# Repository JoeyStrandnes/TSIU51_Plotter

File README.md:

# Skittle Sort

Skittle sort är en sorteringsmaskin för kursen "Mikrodatorprojektet".

- 2x Servomotorer
- 2x ATMega16A
- 3D printad trumma 
- jm162a 2x16 numerisk LCD
- TCS34725 (RGB sensor)

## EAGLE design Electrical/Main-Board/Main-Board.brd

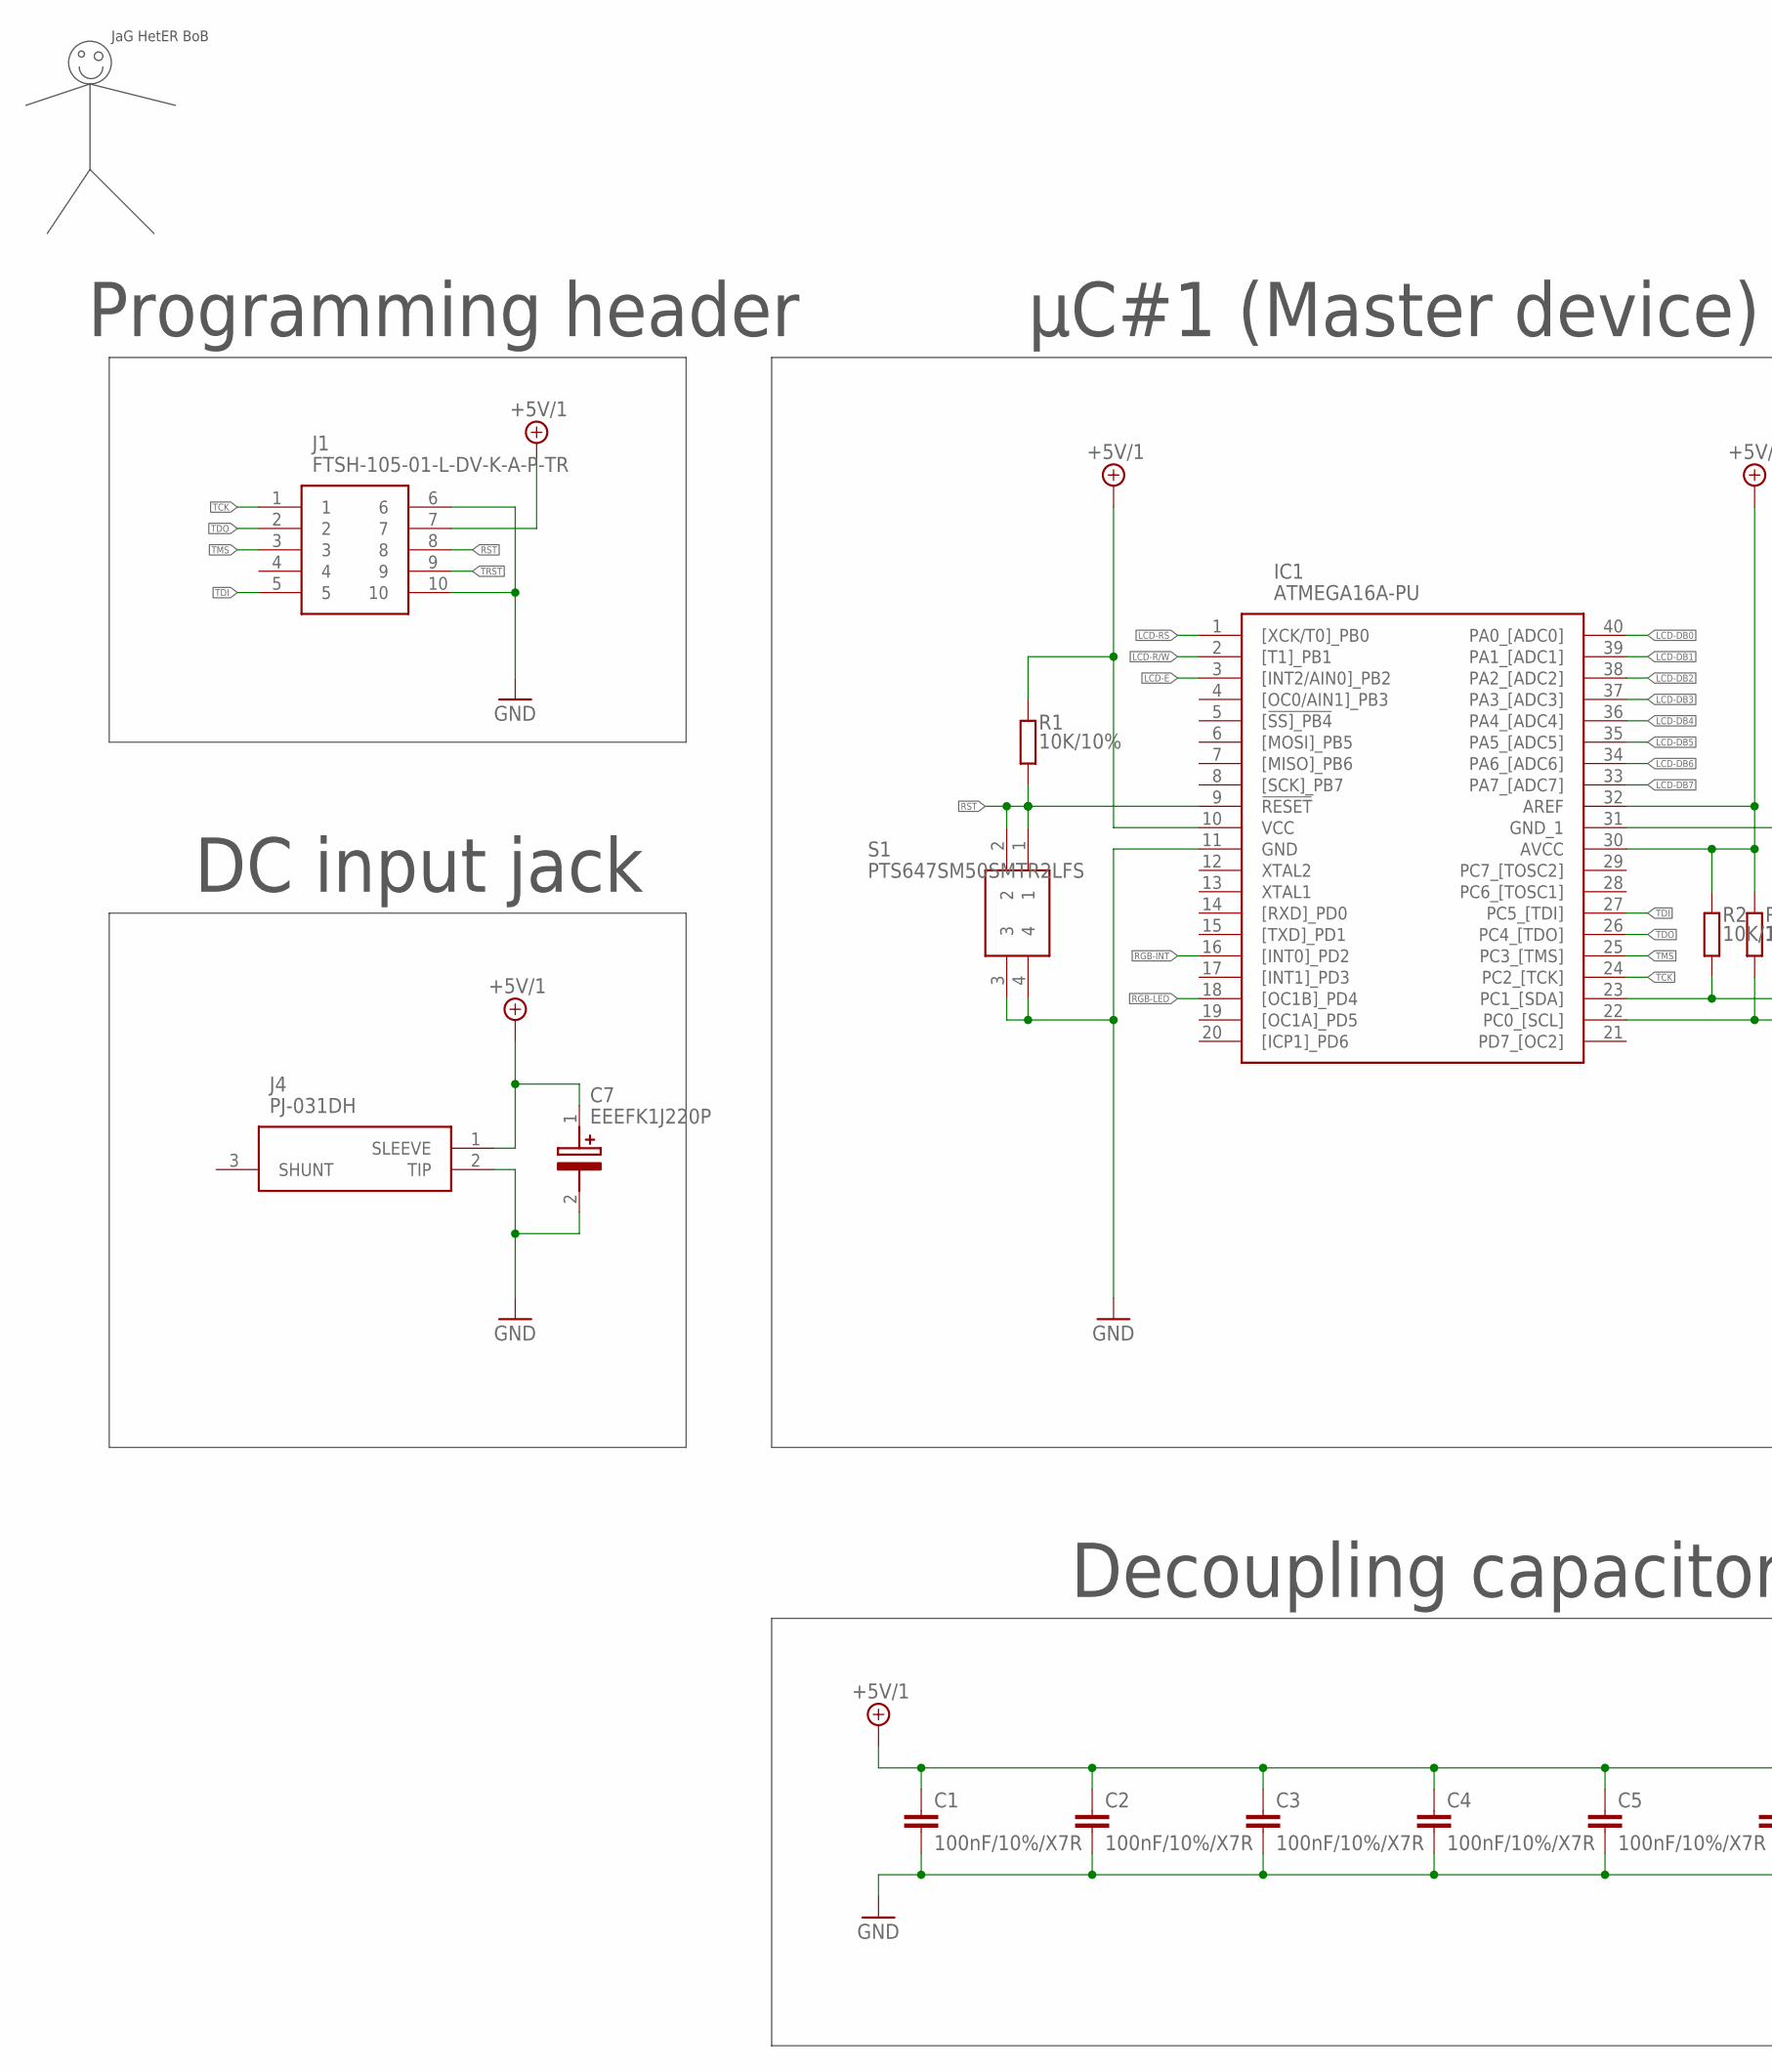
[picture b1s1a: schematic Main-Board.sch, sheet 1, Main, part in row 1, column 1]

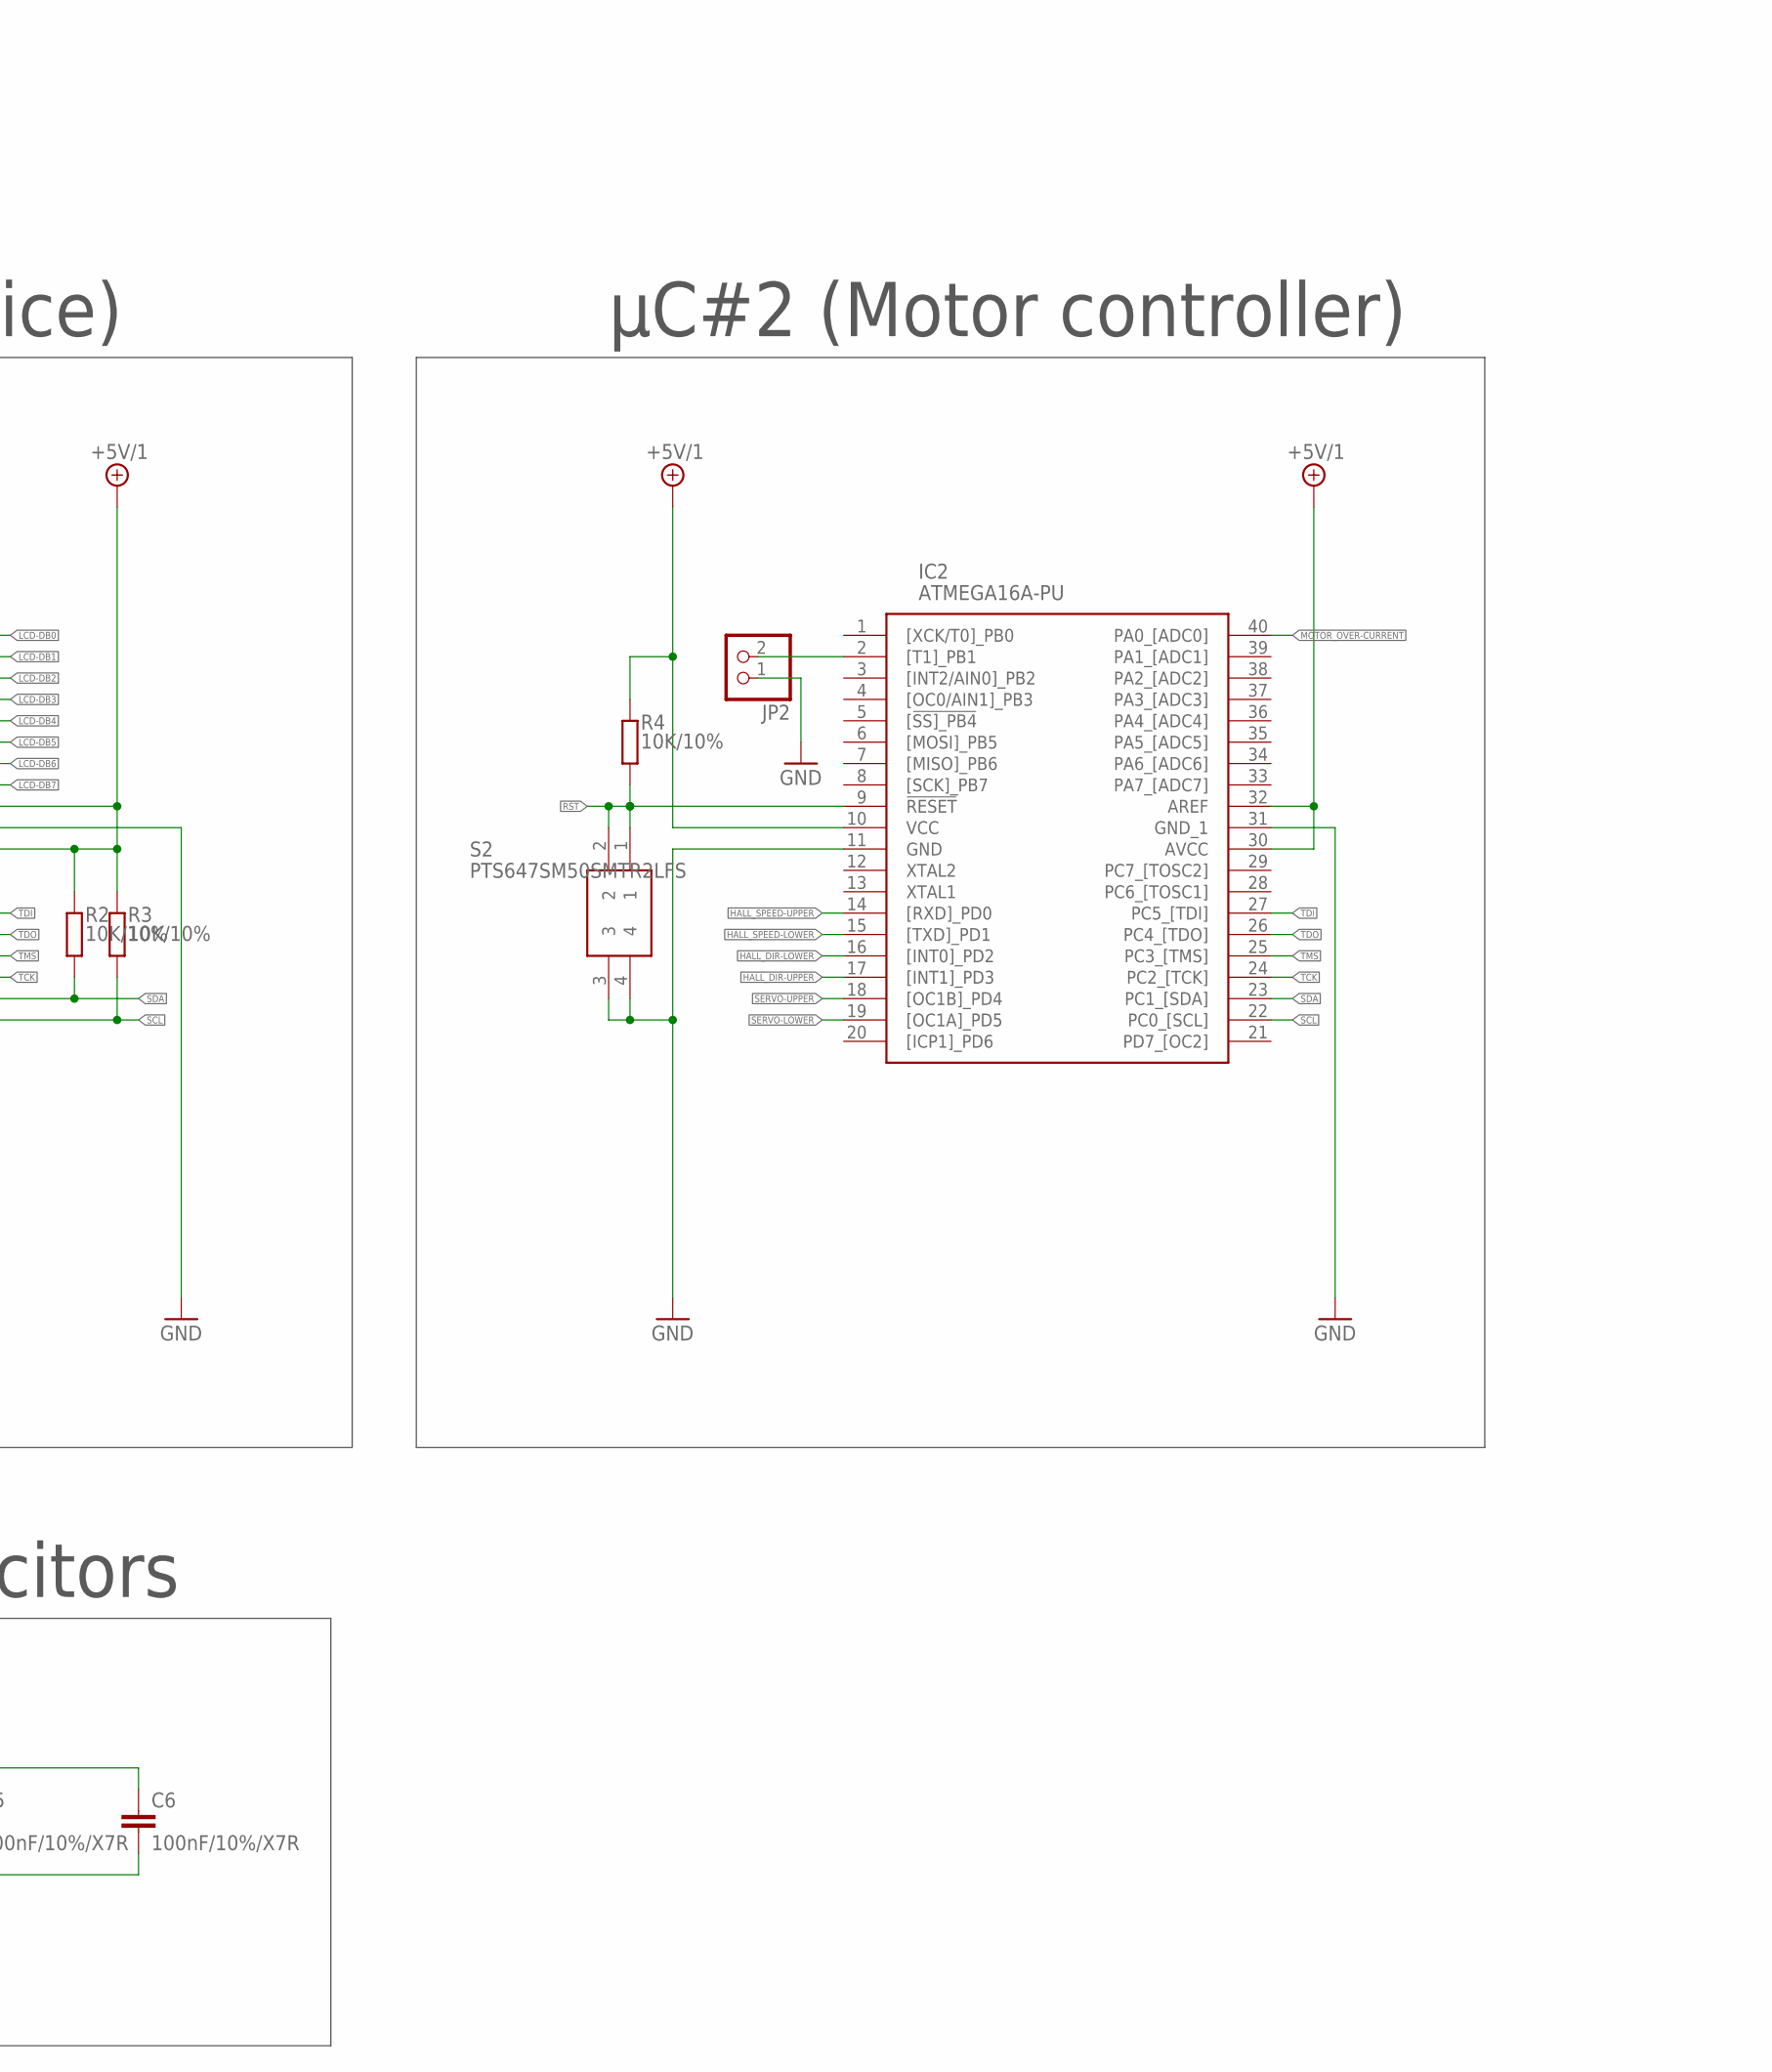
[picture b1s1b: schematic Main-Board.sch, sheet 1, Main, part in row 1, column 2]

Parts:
C1, C2, C3, C4, C5, C6: 100nF/10%/X7R; C0603
C7: EEEFK1J220P; CAPAE800X650N
IC1, IC2: ATMEGA16A-PU; DIP1556W56P254L5232H483Q40N
J1: FTSH-105-01-L-DV-K-A-P-TR; FTSH10501LDVKAPTR
J4: PJ-031DH; PJ031DH
JP2: PINHD-1X2; 1X02
R1, R2, R3, R4: 10K/10%; R0603
S1, S2: PTS647SM50SMTR2LFS

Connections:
+5V/1: C1.1, C2.1, C3.1, C4.1, C5.1, C6.1, C7.1 (+), IC1.10 (VCC), IC1.30 (AVCC), IC1.32 (AREF), IC2.10 (VCC), IC2.30 (AVCC), IC2.32 (AREF), J1.7, J4.1 (SLEEVE), R1.2, R2.2, R3.2, R4.2; also elsewhere on the board
GND: C1.2, C2.2, C3.2, C4.2, C5.2, C6.2, C7.2 (-), IC1.11 (GND), IC1.31 (GND_1), IC2.11 (GND), IC2.31 (GND_1), J1.6, J1.10, J4.2 (TIP), JP2.1, S1.3, S1.4, S2.3, S2.4; also elsewhere on the board
HALL_DIR-LOWER: IC2.16 ([INT0]_PD2); also elsewhere on the board
HALL_DIR-UPPER: IC2.17 ([INT1]_PD3); also elsewhere on the board
HALL_SPEED-LOWER: IC2.15 ([TXD]_PD1); also elsewhere on the board
HALL_SPEED-UPPER: IC2.14 ([RXD]_PD0); also elsewhere on the board
LCD-DB0: IC1.40 (PA0_[ADC0]); also elsewhere on the board
LCD-DB1: IC1.39 (PA1_[ADC1]); also elsewhere on the board
LCD-DB2: IC1.38 (PA2_[ADC2]); also elsewhere on the board
LCD-DB3: IC1.37 (PA3_[ADC3]); also elsewhere on the board
LCD-DB4: IC1.36 (PA4_[ADC4]); also elsewhere on the board
LCD-DB5: IC1.35 (PA5_[ADC5]); also elsewhere on the board
LCD-DB6: IC1.34 (PA6_[ADC6]); also elsewhere on the board
LCD-DB7: IC1.33 (PA7_[ADC7]); also elsewhere on the board
LCD-E: IC1.3 ([INT2/AIN0]_PB2); also elsewhere on the board
LCD-R/W: IC1.2 ([T1]_PB1); also elsewhere on the board
LCD-RS: IC1.1 ([XCK/T0]_PB0); also elsewhere on the board
MOTOR_OVER-CURRENT: IC2.40 (PA0_[ADC0]); also elsewhere on the board
unnamed: IC2.2 ([T1]_PB1), JP2.2
RGB-INT: IC1.16 ([INT0]_PD2); also elsewhere on the board
RGB-LED: IC1.18 ([OC1B]_PD4); also elsewhere on the board
RST: IC1.9 (!RESET), IC2.9 (!RESET), J1.8, R1.1, R4.1, S1.1, S1.2, S2.1, S2.2
SCL: IC1.22 (PC0_[SCL]), IC2.22 (PC0_[SCL]), R3.1; also elsewhere on the board
SDA: IC1.23 (PC1_[SDA]), IC2.23 (PC1_[SDA]), R2.1; also elsewhere on the board
SERVO-LOWER: IC2.19 ([OC1A]_PD5); also elsewhere on the board
SERVO-UPPER: IC2.18 ([OC1B]_PD4); also elsewhere on the board
TCK: IC1.24 (PC2_[TCK]), IC2.24 (PC2_[TCK]), J1.1
TDI: IC1.27 (PC5_[TDI]), IC2.27 (PC5_[TDI]), J1.5
TDO: IC1.26 (PC4_[TDO]), IC2.26 (PC4_[TDO]), J1.2
TMS: IC1.25 (PC3_[TMS]), IC2.25 (PC3_[TMS]), J1.3
TRST: J1.9

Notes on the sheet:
JaG HetER BoB
Programming header
µC#1 (Master device)
µC#2 (Motor controller)
DC input jack
Decoupling capacitors

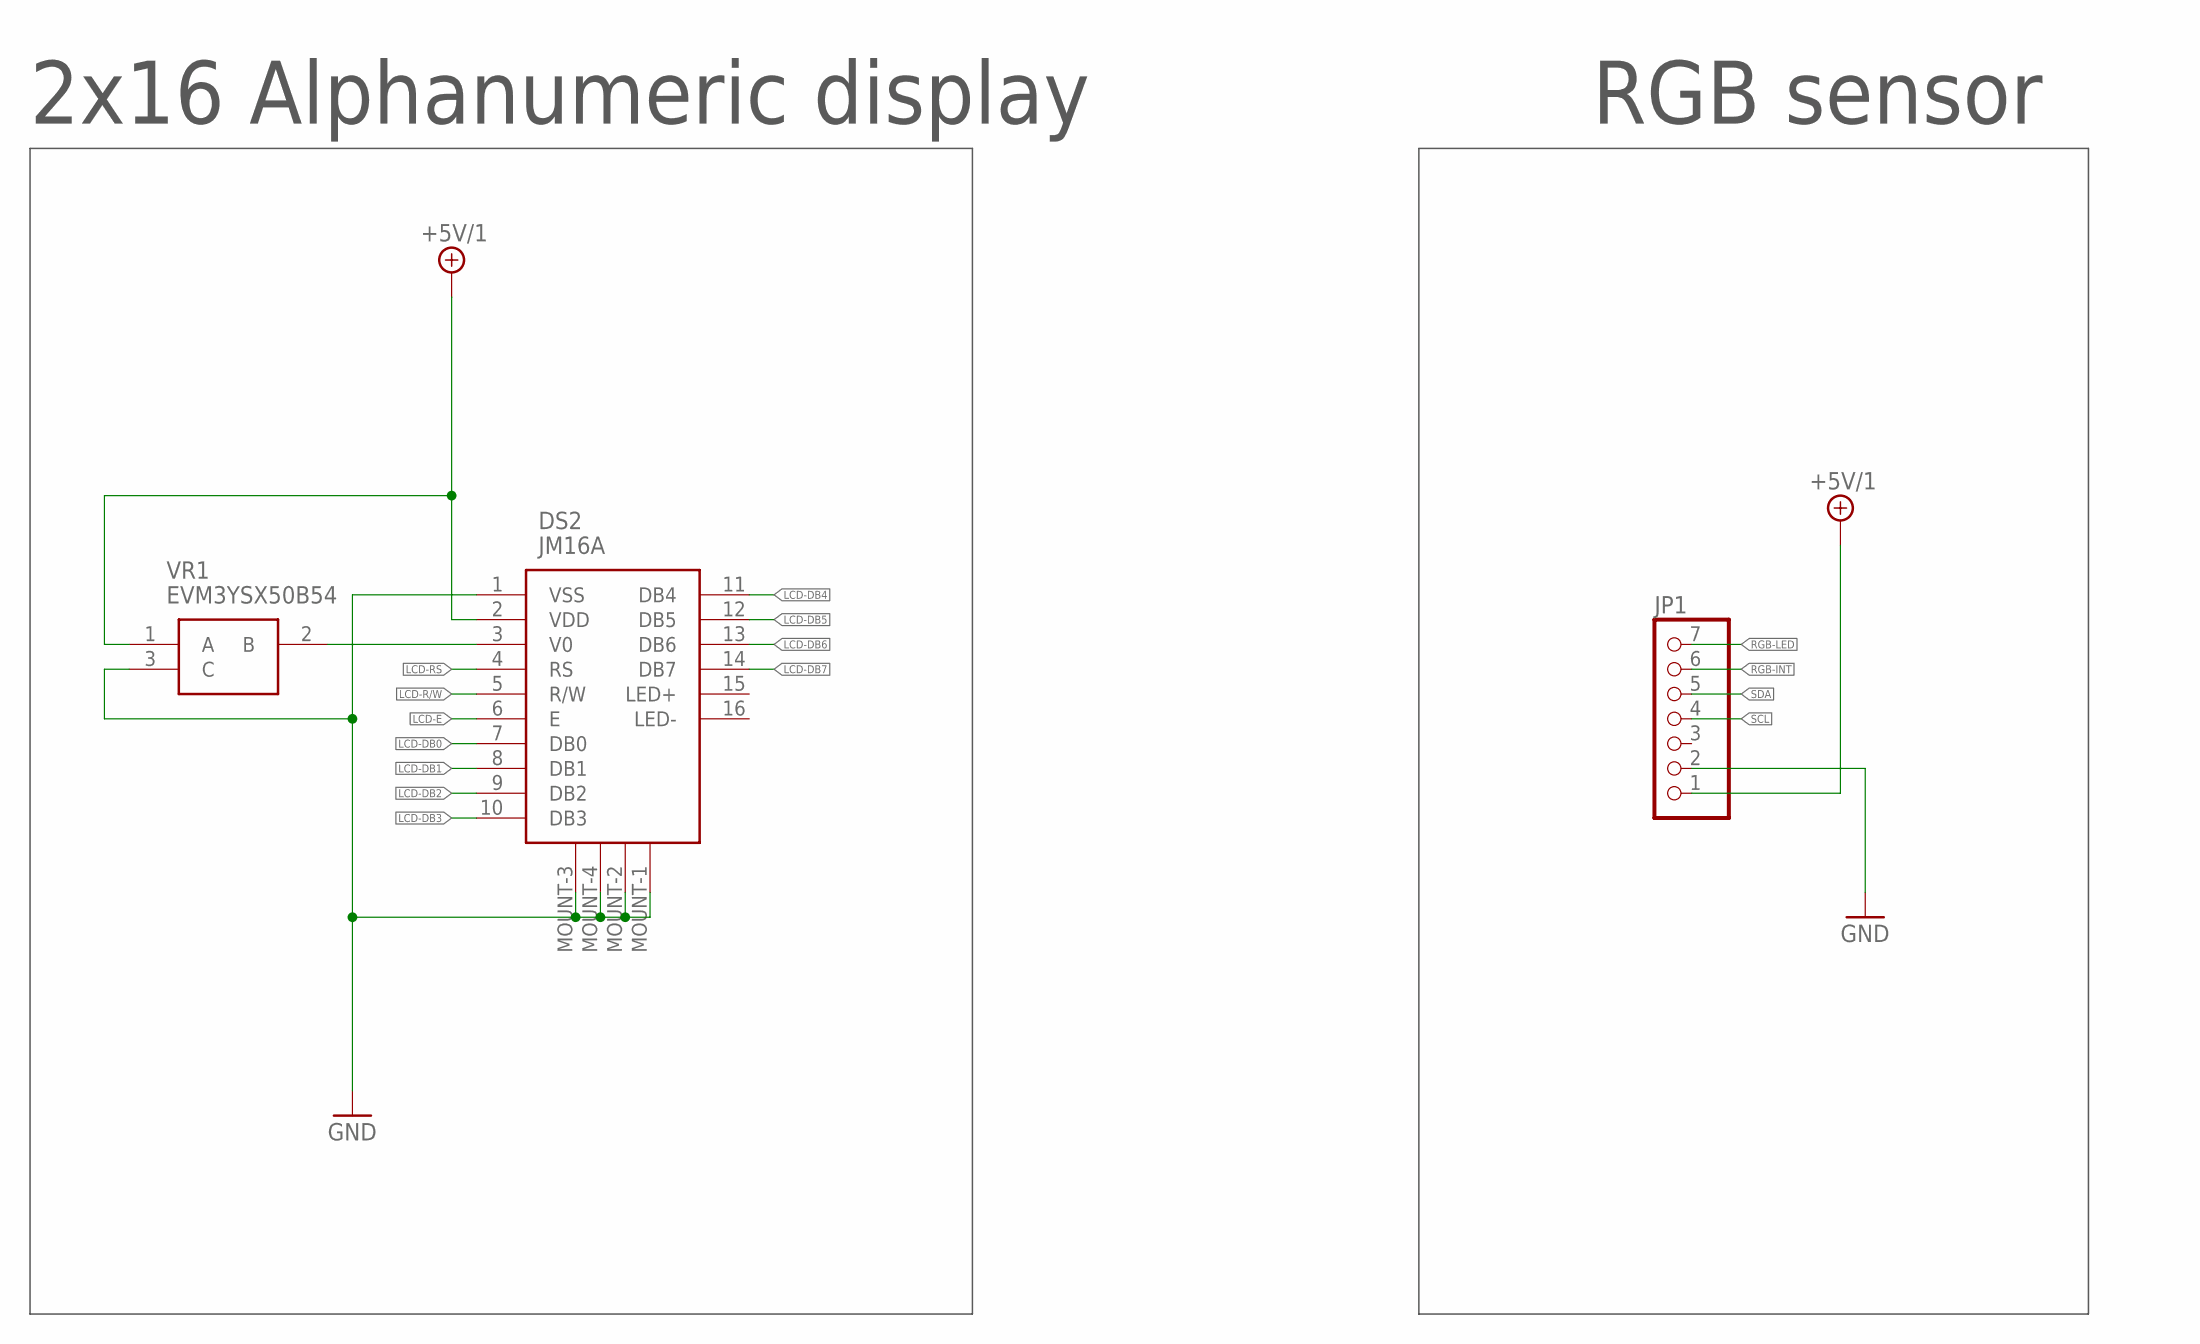
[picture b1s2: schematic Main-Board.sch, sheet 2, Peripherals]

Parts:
DS2: JM16A
JP1: PINHD-1X7; 1X07
VR1: EVM3YSX50B54

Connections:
+5V/1: DS2.2 (VDD), JP1.1, VR1.1 (A); also elsewhere on the board
GND: DS2.1 (VSS), DS2.MOUNT-1 (MOUNT-4), DS2.MOUNT-2 (MOUNT-3), DS2.MOUNT-3 (MOUNT-1), DS2.MOUNT-4 (MOUNT-2), JP1.2, VR1.3 (C); also elsewhere on the board
LCD-DB0: DS2.7 (DB0); also elsewhere on the board
LCD-DB1: DS2.8 (DB1); also elsewhere on the board
LCD-DB2: DS2.9 (DB2); also elsewhere on the board
LCD-DB3: DS2.10 (DB3); also elsewhere on the board
LCD-DB4: DS2.11 (DB4); also elsewhere on the board
LCD-DB5: DS2.12 (DB5); also elsewhere on the board
LCD-DB6: DS2.13 (DB6); also elsewhere on the board
LCD-DB7: DS2.14 (DB7); also elsewhere on the board
LCD-E: DS2.6 (E); also elsewhere on the board
LCD-R/W: DS2.5 (R/W); also elsewhere on the board
LCD-RS: DS2.4 (RS); also elsewhere on the board
unnamed: DS2.3 (V0), VR1.2 (B)
RGB-INT: JP1.6; also elsewhere on the board
RGB-LED: JP1.7; also elsewhere on the board
SCL: JP1.4; also elsewhere on the board
SDA: JP1.5; also elsewhere on the board

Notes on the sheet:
2x16 Alphanumeric display
RGB sensor

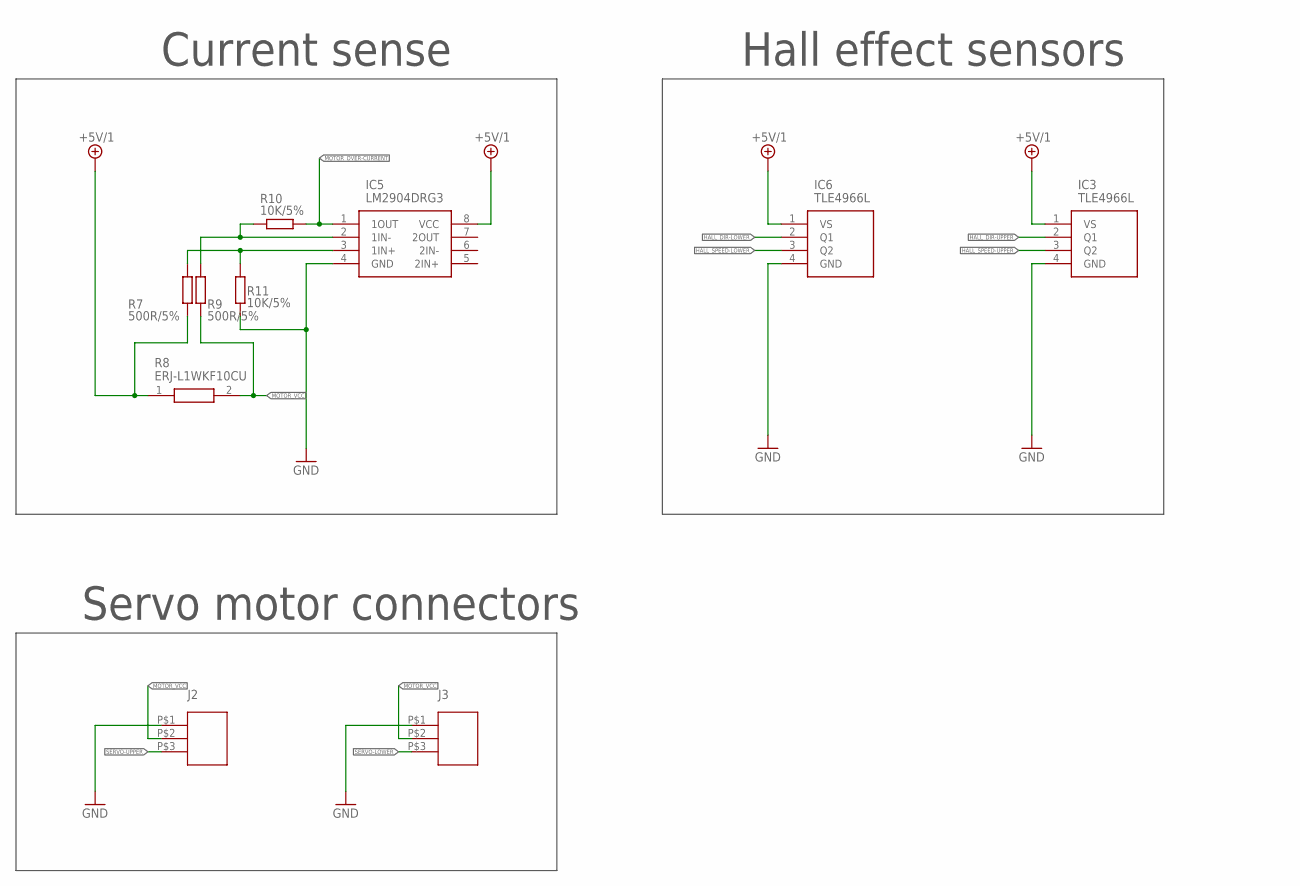
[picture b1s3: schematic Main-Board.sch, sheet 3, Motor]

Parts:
IC3, IC6: TLE4966L
IC5: LM2904DRG3; SOIC127P600X175-8N
J2, J3: 0022288033
R7, R9: 500R/5%; R0603
R8: ERJ-L1WKF10CU; RESC6332X120N
R10, R11: 10K/5%; R0603

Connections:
+5V/1: IC3.1 (VS), IC5.8 (VCC), IC6.1 (VS), R7.1, R8.1 (R1); also elsewhere on the board
GND: IC3.4 (GND), IC5.4 (GND), IC6.4 (GND), J2.P$1 (1), J3.P$1 (1), R11.1; also elsewhere on the board
HALL_DIR-LOWER: IC6.2 (Q1); also elsewhere on the board
HALL_DIR-UPPER: IC3.2 (Q1); also elsewhere on the board
HALL_SPEED-LOWER: IC6.3 (Q2); also elsewhere on the board
HALL_SPEED-UPPER: IC3.3 (Q2); also elsewhere on the board
MOTOR_OVER-CURRENT: IC5.1 (1OUT), R10.2; also elsewhere on the board
MOTOR_VCC: J2.P$2 (2), J3.P$2 (2), R8.2 (R2), R9.1
unnamed: IC5.3 (1IN+), R7.2, R11.2
unnamed: IC5.2 (1IN-), R9.2, R10.1
SERVO-LOWER: J3.P$3 (3); also elsewhere on the board
SERVO-UPPER: J2.P$3 (3); also elsewhere on the board

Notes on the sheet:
Current sense
Hall effect sensors
Servo motor connectors

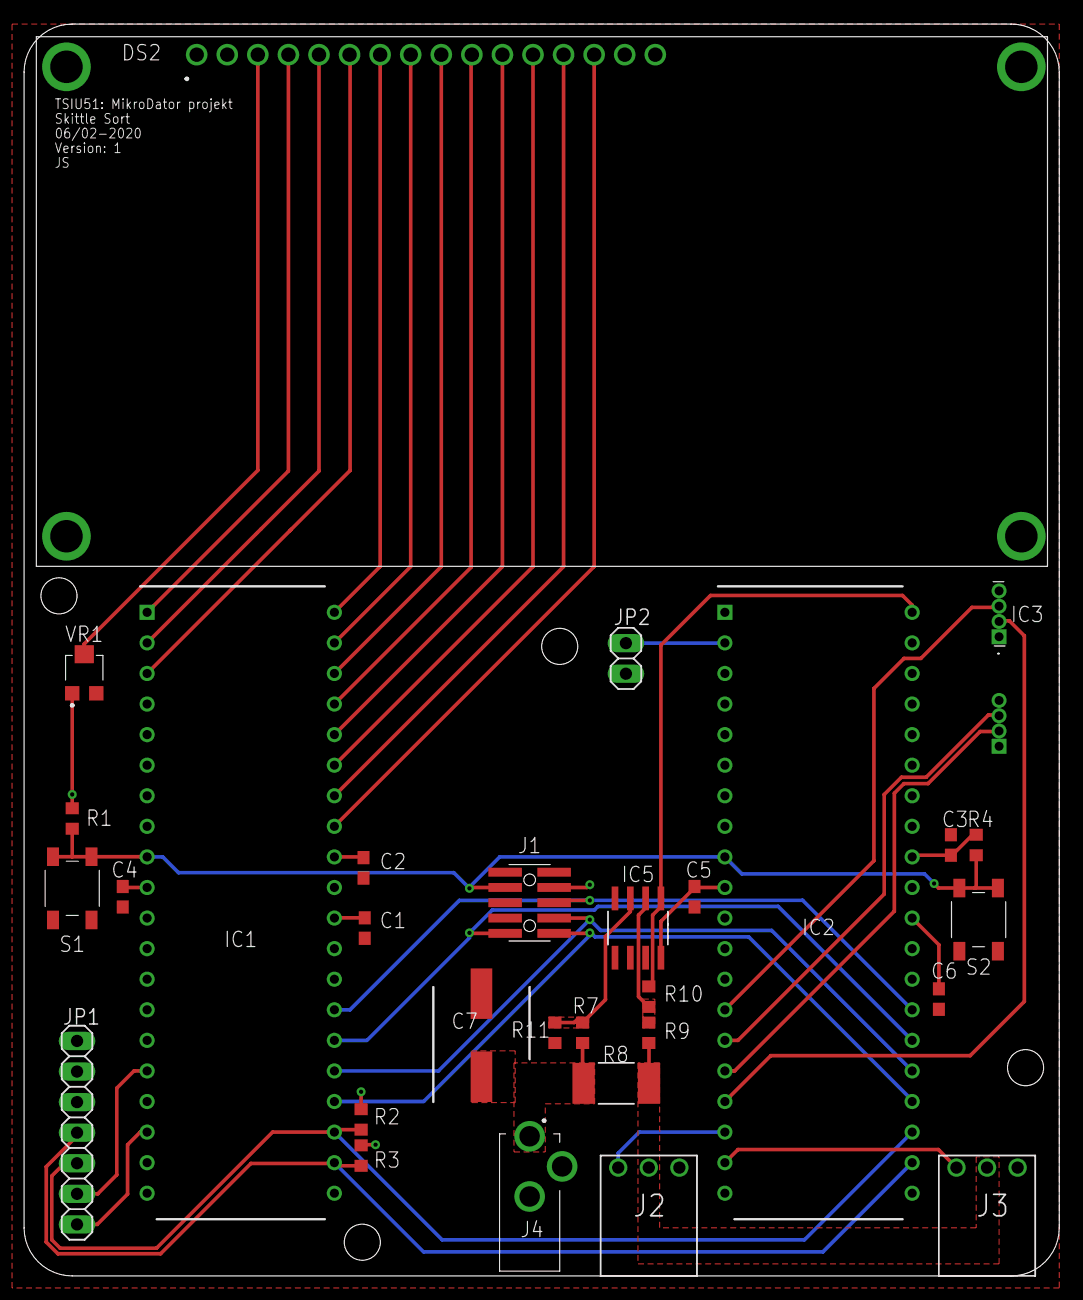
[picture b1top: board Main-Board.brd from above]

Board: 2 copper layers, 86.0 x 104.0 mm, 31 parts (1 on the bottom side), 34 nets.

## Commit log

2020-01-23 Initial software commit
2020-01-23 Initial funnel commit
2020-01-23 Initiation of PCB project files
2020-01-24 Kravspec Init
2020-01-24 Updated and added more explenations
2020-01-25 Added an alternative spec and flow chart
2020-01-25 Updated alternative specs
2020-01-25 Updated teh funnel to support teh size of the skittles, also added a skittle
2020-01-25 From Vanheden
2020-01-25 Added upper disk
2020-01-25 Added lower disk and removed temp file
2020-01-25 Added RGB-sensor specs
2020-01-25 Added temporary motor and updated Lower Disk
2020-01-25 Added proof of concept slide
2020-01-25 Från Vanheden
2020-01-25 Osäker på relevans
2020-01-25 Första försök till LCD-drivers
    Enbart kollat i databladen och föreläsnings-pdf och utgått ifrån det. Kompilerad i simulatorn
2020-01-25 Added Manufacturers CAD-Files
2020-01-25 Updated mechanical components
2020-01-25 Updated assembly
2020-01-27 ignore .tmp files
2020-01-27 Börja på motor processor
2020-01-27 Updated shape
2020-01-27 Updates and refined mechanical components
2020-01-28 Börja på motor microkontroll
2020-01-28 Börja på mikrodator 2
2020-01-28 Fungera fyfan
2020-01-28 Updated schematic and ignore all backup files
2020-01-28 Updated schematic
2020-01-28 Lite med timers
2020-01-28 Updated schematic
    Added a similar LCD and µC:2
2020-01-28 Added motor things to schematic
2020-01-28 Servo controll continue
2020-01-28 Did some layout
2020-01-29 Updated layout
2020-01-29 Prelimenary layout
2020-01-29 Allmän förbättring.
    Kopplar loss DDR när det inte skrivs. Bör fungera irl?
2020-01-29 Updated mechanical parts
2020-01-29 mer av samma chip, kanske är användbart
2020-01-30 Added schematic pdf
2020-01-30 Uppdaterad kravspec. Skickat till Micke
2020-01-30 Fungerade i MUXEN med Daliakortet!
2020-01-30 Updated schematci for more componenets
2020-01-30 Added temp BOM from EAGLE
2020-01-30 Create Motor lite bättre
2020-01-30 Funderat på datastruktur och förbättring
    Lagt till ett försök till att läsa DDRAM-addresen
2020-02-01 Updated mechanical files, with a semi new solution
2020-02-01 Only need to add funnel
2020-02-03 VI ANVÄNDER DENNA!!!
2020-02-03 uppdaterad
2020-02-03 la till på interupten
2020-02-04 Create main.asm
    Basic TWI MT code
2020-02-04 Update main.asm
    Test av TWI mellan ATMEGA och RGB
2020-02-04 FUNGERAR!
    1MHz i atmegan.
2020-02-05 Added dummy for consistent results
2020-02-05 Nice version!
2020-02-05 Update Motor lite bättre
    Lite mer
2020-02-05 Added the final components to the schmatic and updated the layout
2020-02-05 Work in progress layout
2020-02-06 Working
2020-02-06 Now fully working
2020-02-06 LCD is wrong, need to finish teh new footprint for it.
2020-02-06 MASSA NYA FUNKTION FUNKAR IBLAND
2020-02-06 Updated display footprint and fixed layout to suit it.
2020-02-06 Final PCB. Added GERBER files for MF
2020-02-07 Update Motor lite bättre
    Ännu lite bättre
2020-02-10 Enlarged servo motor mount
2020-02-10 Made some changes to the contruction
2020-02-10 Kod för en avlässning. Kanske fungerar.
2020-02-13 Create READ6REG.asm
    Läs 6 reg
2020-02-13 Fixat fel funkar typ ger 0A
2020-02-14 Added push/pop and byte output to LCD for debuging
2020-02-14 Fixed push overflow, works!
2020-02-20 Added bottom slide part
    Going to split it to make it easier to print
2020-02-20 Fungerar, skriver ut data den får
2020-02-20 Updated bottom slide model and added STL file
2020-02-23 Updated slide assembly, added a color for the shaft, added RGB sensor and added magnet placement/ hall sensor
2020-02-23 Lagt till Push/pop, Wait-funktion. Utveckla denna!
    Lagt till modulär Wait-funktion som beror på Atime. Mer konstanter och config uppe i början av programmet. RGB_INIT, RGB_SHUTDOWN och börjat så smått på ERROR_HANDLING på TWI.
2020-02-24 Lagt till utformningen på skärmen, funkar!
    Ska lägga till en funktion som läser en byte från /COLOR/_N och skriver ut i binärt med 2 värdesiffror efter varje färg
2020-02-24 Lite bättre
2020-02-24 Added STL files
2020-02-24 Ger logiska värden! NICE!!!
    ATIME måste vara 0x00!!! READ6REGISTERS verkade funka när vi fixade ett fel!
2020-02-24 speaker
2020-02-24 Updated model and added mounting points for RGB sensor and the hall effect sensor
2020-02-25 Gain config added. Läser alla 8 Byte
2020-02-27 Lagt till utskrift av antal Skittles i BCD
    Rensat bort gammal kod. Är i stort sett färdig att kombineras med resten av projektet.
2020-03-03 Enlarged hole for RGB sensor
2020-03-04 Main_nr2
    hela microcontroller 2 med många problem med magneter
2020-03-05 Update Main_nr2
    FIxa start, fungerar!!!
2020-03-06 Combined lcd and rgb-sensor
    🗡
2020-03-06 Updated Slide-Top to mount a funnel to it
2020-03-07 16bit
2020-03-07 Update Speaker
    Fixa högtalare
2020-03-07 typ sortering fast ändå inte
    skjut mig
2020-03-08 First draft Presentation
2020-03-08 Added images and updated model for exploded view, also added it to the prsentation
2020-03-08 Lagt till Normalisering, ändrat fel i Lookup-tabell
    Lagt till 16 bit multiplikation från biblioteket, används inte än dock.
2020-03-09 Added images andupdated presentation
2020-03-09 Litet skit!
2020-03-09 Förbättringar, komplett?
    Nya ref-värde, Uppdatera antal skittle till skärmen. Modulär Clear Sram
2020-03-09 16x16 multi funkar, blir mindre avrundningsfel!
    Använder resten från vår 16x16 division till att öka precisionen.
    Lagt till push o pops för att öka till snart 1400 rader X)
    ZZZZZZZZZZZZZZZZZZZZZZZZZZZZZZZZZ
2020-03-10 FINFINT
    Strukturerat var koden ligger för tydlighet.
    Lagt till avrundning i min Divide_by_precision
    Snyggat till Compare och dess underfunktioner och gjorde dom mer strukturerade
2020-03-10 Sorterar och sånt
    Fixat off-by-one vid start!
    Lagt till Vilket håll den ska snurra i I2C interupten
2020-03-10 kretskort bild
2020-03-10 Added software slides
2020-03-10 Bild till pp
2020-03-10 färgDonuts
2020-03-10 Delete
2020-03-10 The real colorDonuts
2020-03-10 Flow chart INIT
2020-03-10 Image test
2020-03-10 Added images
2020-03-10 Skittle I krubba
2020-03-10 Added funnel rtaiuner and updated funnel
    Also added some renderings to the image collection
2020-03-11 Added stl file
2020-03-11 Added Cup STL
2020-03-11 Problem med allt
    :¨¨(
2020-03-11 Uppdaterat med nya referensvärden!
    =D
2020-03-12 16x16 multiplikation
    Får ev ändra vilka register den använder. Får avvakta tills den nya divisionen funkar???
2020-03-12 nytt namn
2020-03-12 Cirkus
2020-03-12 Lagt till den nya 16x16 multiplikationen
    Snyggat till lite där det var felstavningar och sånt
2020-03-12 Fixat puls till MasterMC och lagt till musik
2020-03-12 Lagt till No_Skittle "Färg" och gjort den lite modulär
2020-03-12 Utökat Difference i SRAM till 16bit
    Nästa steg är att skapa weights för de olika Differences?
2020-03-13 hmmmmm funderar på nytt mätsätt med cleardata
2020-03-13 song
2020-03-13 Lagt till TWI ERROR HANDLER
    Skriver ut på LCD om nån TWI gick åt helvete. Nya mätvärden utan tratt och funkar okej. Med tratt blir allt Purple.
2020-03-13 Sänkt hastighet på CCW. GÖRA OLIKA HASTIGHETER FÖR ÖVRE/UNDRE?
    Fick ändra stop-värdet då den drifta lite. Sänkte hastigheten rejält på övre trumman så den stannar exaktare framför sensorn.
2020-03-15 Räknar med Clear Diff. Kan se Mätdata på LCD, NY BCD till LCD-funktion
    Räknar ut clear diff och dividerar ner till valfri multipel av 2. Därför är Clearvärdena inte längre uppskalade i Lookup-tablen. Skalas upp i Normalize_Data istället. Får se om detta hjälper.
    Har även lagt till funktion som skriver CRGBDATA (rådata) till skärmen så vi kan debugga. Fick då skriva en ny funktion som printar 3 siffror till skärmen får det ska funka.
2020-03-17 lite bilder
2020-03-18 FINAL
2020-03-20 Nya mätvärden
    Ful-lösning på att skicka NO_SKITTLE. Skickar den som lila. Funkar mycket bra
2020-03-20 Lagt till separat hastighet för den undre disken CCW, men den fucka upp när den gick för snabbt baklänges...Är därför samma
    Gör även kontroll i början om den övre diskan fortfarande snurrar och skickar då inte startpuls till mastern
2020-03-20 Lagt till Demo så den slumpar lite snurr när den inte får någon skittle
2020-03-31 Demo-versionen som slumpar snurr när den inte får någon SKittle
    Råkade ladda upp projektfilen förra veckan :S
2020-03-31 Fel uppladdning
2020-03-31 Added halleffect sensor visuals for bottom disk
2020-03-31 Added all induvidual schematic images
2020-03-31 Added GIF
2020-03-31 ändra lite fel i kommentarerna
2020-04-03 LCD bilder
2020-04-03 Snyggade till lite och tog bort debugfunktioner
2020-04-03 Mer bilder
2020-04-05 More images
2020-04-10 MCU1 Snyggat till koden och lagt den på sitt riktiga ställe
2020-04-10 heter nu MASTER
2020-04-10 Ändrade jJSP och lade till lite bilder
2020-04-10 Litet fel fixat
2020-04-15 fixa ett namnfel
2020-04-15 Create Piechart_6colors.png
    bild
2020-05-08 Flyttade en bild som hamnat fel
2020-05-17 Uppdaterade några ritningar
2020-05-19 Lade till tabb istället för mellanslag. La även in den långsamma versionen av divison så micke blir glad
2020-05-19 fixade lite bilder
2020-05-21 Fix fel i bild
    fixade blockschema och lite bilder
2020-05-22 förtydligade i kommentarerna, var väldigt förvirrande
2020-09-01 lol hade lite kvar
    whatever lite sånt som jag croppat
